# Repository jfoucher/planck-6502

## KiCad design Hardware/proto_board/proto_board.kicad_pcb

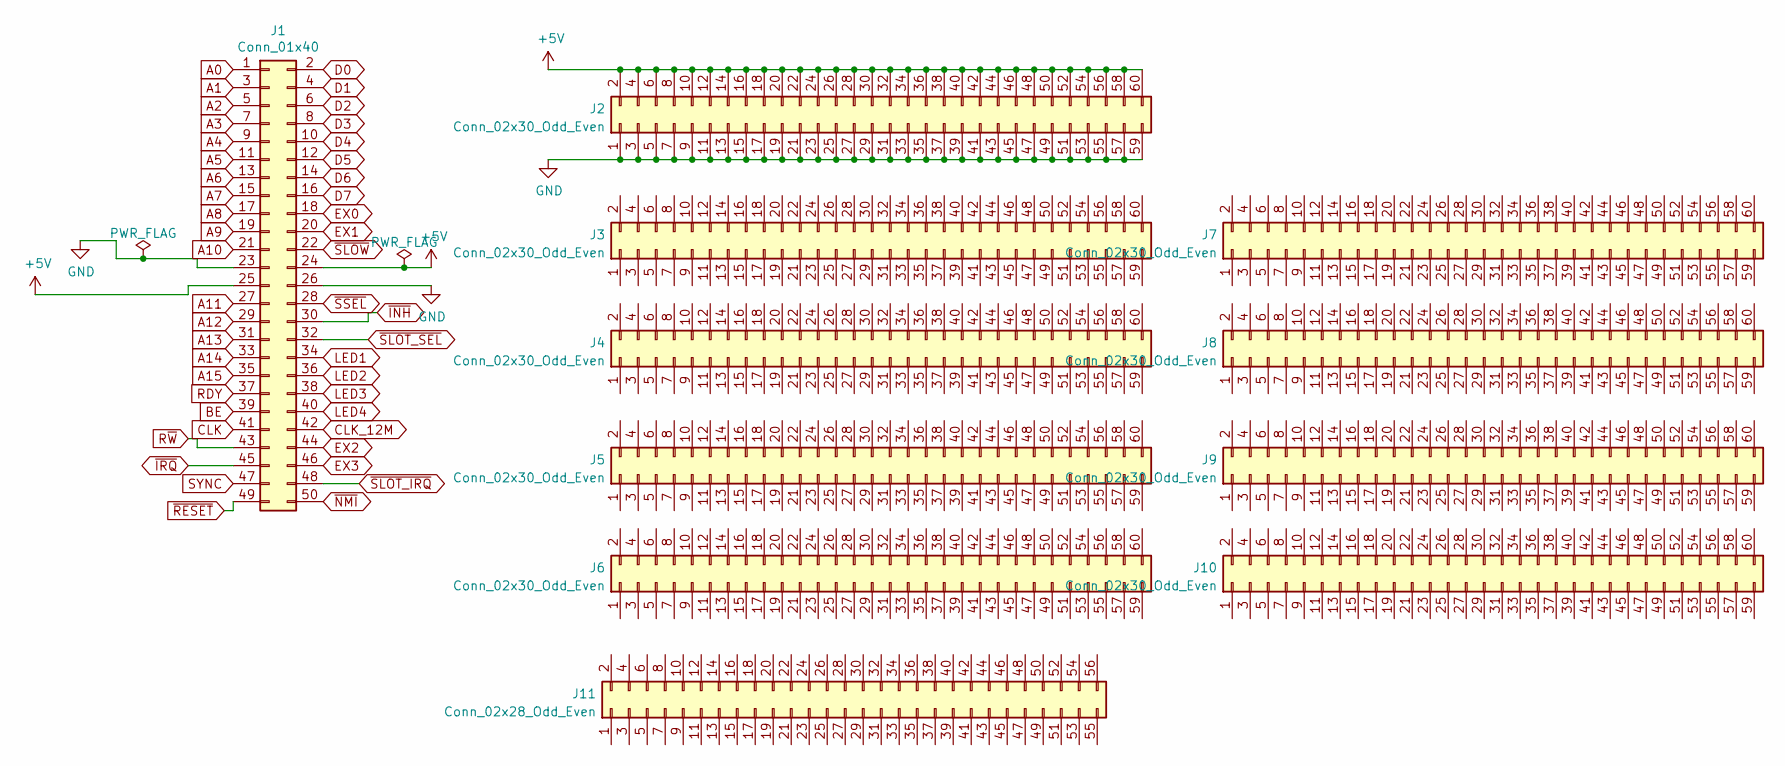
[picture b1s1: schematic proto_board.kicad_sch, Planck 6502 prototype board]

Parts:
J1: Conn_01x40; PinHeader_2x25_P2.54mm_Horizontal
J2, J3, J4, J5, J6, J7, J8, J9, J10: Conn_02x30_Odd_Even; PinHeader_2x30_P2.54mm_Vertical
J11: Conn_02x28_Odd_Even; PinHeader_2x28_P2.54mm_Vertical

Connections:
+5V: J1.24, J1.25, J2.2, J2.4, J2.6, J2.8, J2.10, J2.12, J2.14, J2.16, J2.18, J2.20, J2.22, J2.24, J2.26, J2.28, J2.30, J2.32, J2.34, J2.36, J2.38, J2.40, J2.42, J2.44, J2.46, J2.48, J2.50, J2.52, J2.54, J2.56, J2.58, J2.60
A0: J1.1
A1: J1.3
A2: J1.5
A3: J1.7
A4: J1.9
A5: J1.11
A6: J1.13
A7: J1.15
A8: J1.17
A9: J1.19
A10: J1.21
A11: J1.27
A12: J1.29
A13: J1.31
A14: J1.33
A15: J1.35
BE: J1.39
CLK: J1.41
CLK_12M: J1.42
D0: J1.2
D1: J1.4
D2: J1.6
D3: J1.8
D4: J1.10
D5: J1.12
D6: J1.14
D7: J1.16
EX0: J1.18
EX1: J1.20
EX2: J1.44
EX3: J1.46
GND: J1.23, J1.26, J2.1, J2.3, J2.5, J2.7, J2.9, J2.11, J2.13, J2.15, J2.17, J2.19, J2.21, J2.23, J2.25, J2.27, J2.29, J2.31, J2.33, J2.35, J2.37, J2.39, J2.41, J2.43, J2.45, J2.47, J2.49, J2.51, J2.53, J2.55, J2.57, J2.59
LED1: J1.34
LED2: J1.36
LED3: J1.38
LED4: J1.40
RDY: J1.37
R~W: J1.43
SYNC: J1.47
~INH: J1.30
~IRQ: J1.45
~NMI: J1.50
~RESET: J1.49
~SLOT_IRQ: J1.48
~SLOT_SEL: J1.32
~SLOW: J1.22
~SSEL: J1.28

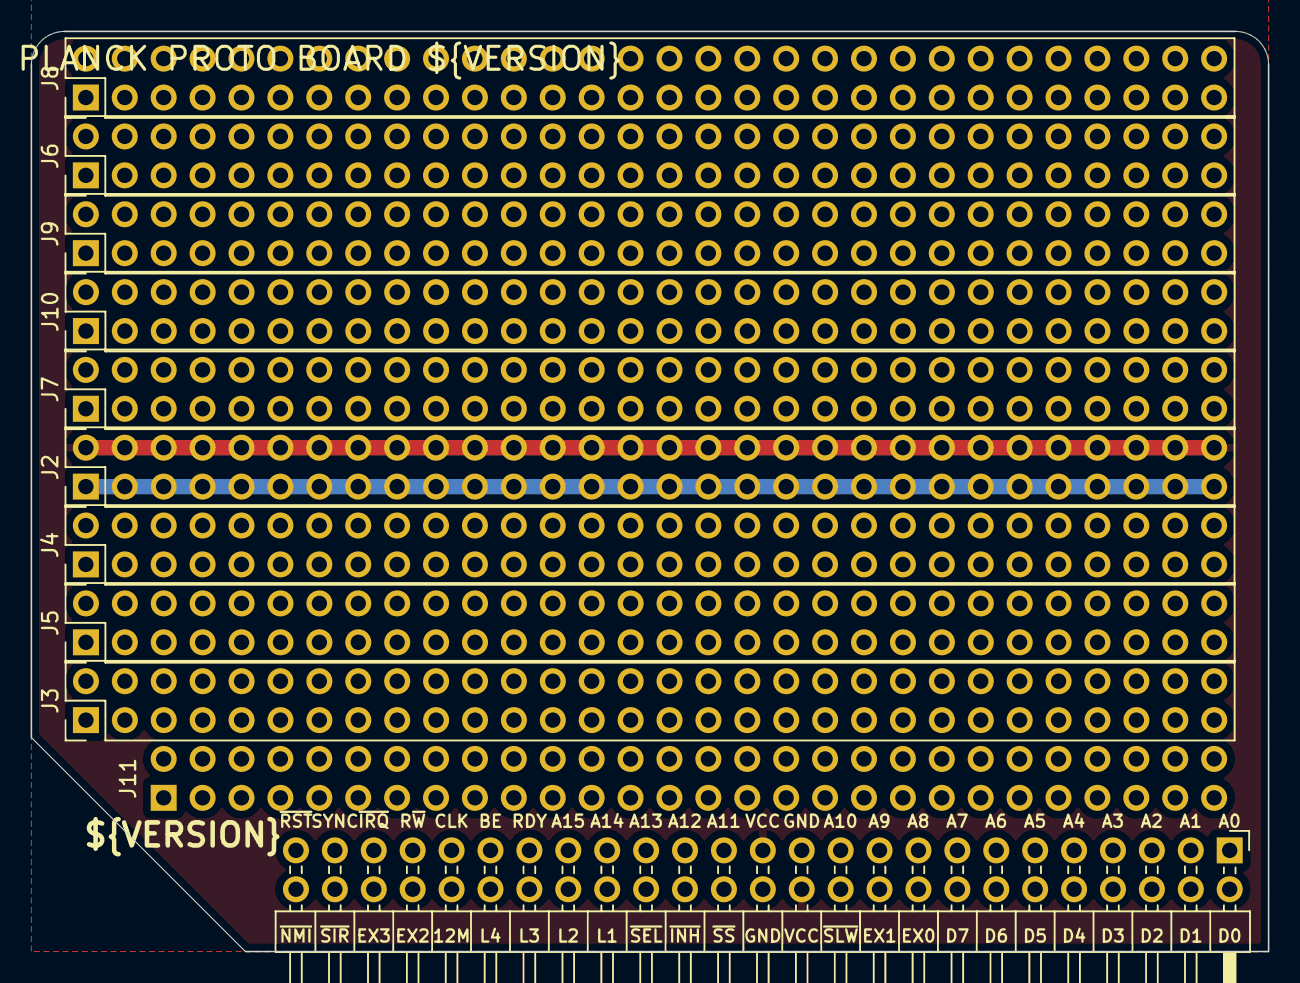
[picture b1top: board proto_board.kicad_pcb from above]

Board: 2 copper layers, 80.8 x 60.1 mm, 11 parts (0 on the bottom side), 2 nets.

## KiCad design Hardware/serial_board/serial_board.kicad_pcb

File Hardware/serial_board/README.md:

## Planck 6502 Serial board

This board uses a DWC 6551 chip to provide a serial port for the computer. It accepts a TTL serial to usb adapter.

This is what the board looks like at the moment

<br />This documentation is licensed under a <a rel="license" href="http://creativecommons.org/licenses/by-sa/4.0/">Creative Commons Attribution-ShareAlike 4.0 International License</a>.

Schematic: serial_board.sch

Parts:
C1, C2: C_Small; C_Disc_D4.3mm_W1.9mm_P5.00mm
D1, D2: LED; LED_D3.0mm
J1: Conn_01x40; PinHeader_2x25_P2.54mm_Horizontal
J2: Conn_01x06; PinSocket_1x06_P2.54mm_Vertical
R1, R2: 330R; R_Axial_DIN0204_L3.6mm_D1.6mm_P5.08mm_Horizontal
R3, R4: 10k; R_Axial_DIN0204_L3.6mm_D1.6mm_P5.08mm_Horizontal
U1: W65C51NxP; DIP-28_W15.24mm_Socket
X1: CXO_DIP8; Oscillator_DIP-8

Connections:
+5V: C1.1, C2.1, J1.24, J1.25, J2.4, R3.2, U1.15 (VCC), X1.8 (Vcc)
/RX: D2.2, J2.3, U1.12 (RxD)
/TX: D1.2, J2.2, U1.10 (TxD)
/~DSR~: J2.1, R4.2, U1.17 (~DSR)
/~DTR~: U1.11 (~DTR)
/~RTS~: J2.5, U1.8 (~RTS)
A0: J1.1, U1.13 (RS0)
A1: J1.3, U1.14 (RS1)
A2: J1.5
A3: J1.7
A4: J1.9
A5: J1.11
A6: J1.13
A7: J1.15
A8: J1.17
A9: J1.19
A10: J1.21
A11: J1.27
A12: J1.29
A13: J1.31
A14: J1.33
A15: J1.35
BE: J1.39
CLK: J1.41, U1.27 (ϕ2)
CLK_12M: J1.42
D0: J1.2, U1.18 (D0)
D1: J1.4, U1.19 (D1)
D2: J1.6, U1.20 (D2)
D3: J1.8, U1.21 (D3)
D4: J1.10, U1.22 (D4)
D5: J1.12, U1.23 (D5)
D6: J1.14, U1.24 (D6)
D7: J1.16, U1.25 (D7)
EX0: J1.18
EX1: J1.20
EX2: J1.44
EX3: J1.46
GND: C1.2, C2.2, J1.23, J1.26, J2.6, R1.1, R2.1, R4.1, U1.1 (VSS), U1.9 (~CTS), U1.16 (~DCD), X1.4 (GND)
LED1: J1.34
LED2: J1.36
LED3: J1.38
LED4: J1.40
unnamed: D1.1, R1.2
unnamed: D2.1, R2.2
unnamed: R3.1, U1.2 (CS1)
unnamed: U1.6 (XTAL1), X1.5 (OUT)
RDY: J1.37
R~W~: J1.43, U1.28 (R/~W)
SYNC: J1.47
~INH~: J1.30
~IRQ~: J1.45
~NMI~: J1.50
~RESET~: J1.49, U1.4 (~RES)
~SLOT_IRQ~: J1.48, U1.26 (~IRQ)
~SLOT_SEL~: J1.32, U1.3 (~CS2)
~SLOW~: J1.22
~SSEL~: J1.28

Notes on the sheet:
Added pullup here

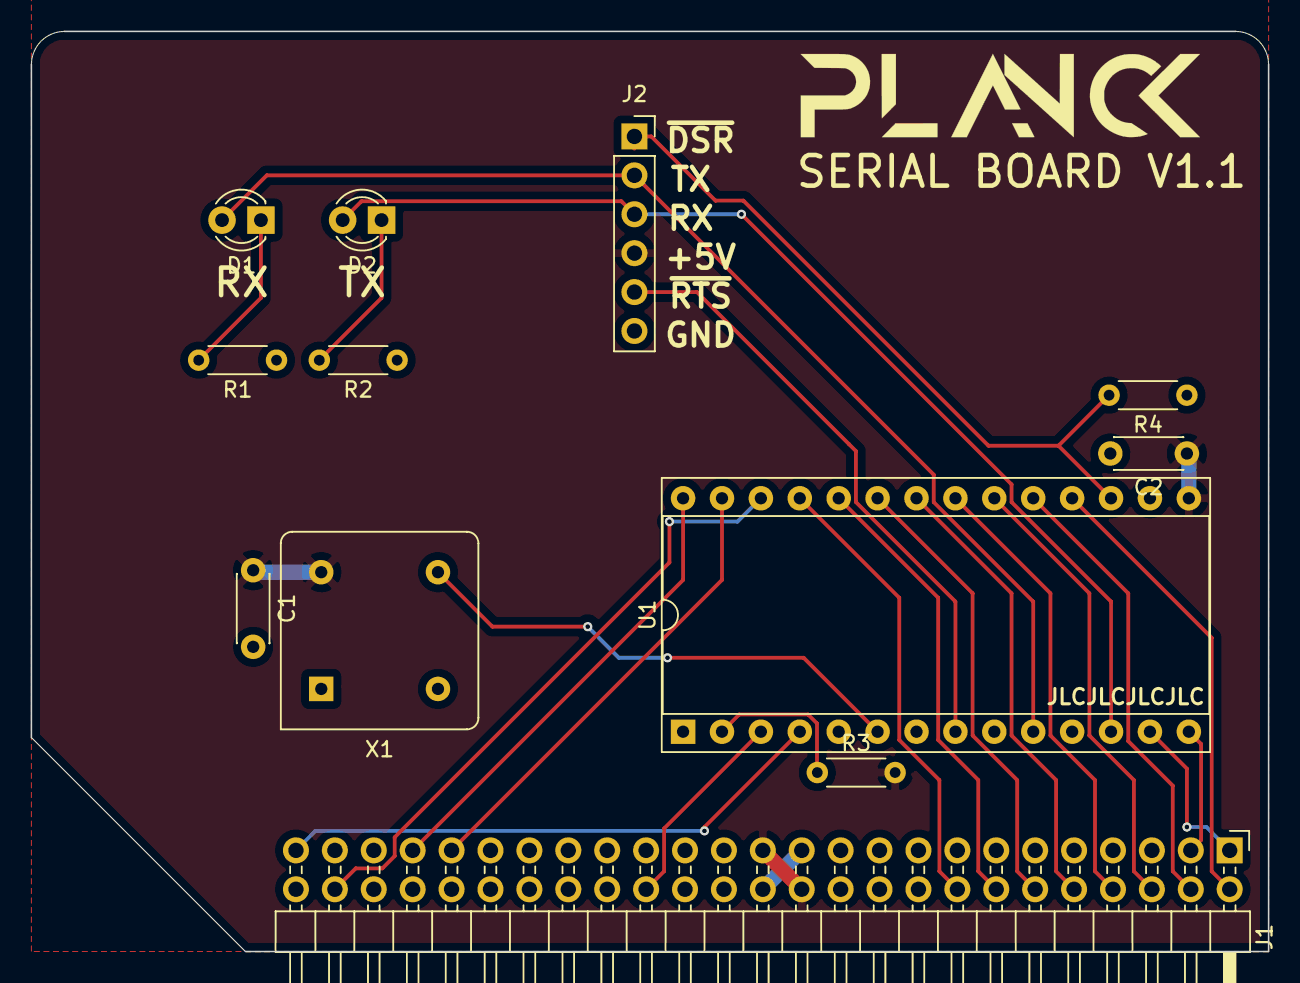
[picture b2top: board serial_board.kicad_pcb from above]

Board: 2 copper layers, 80.8 x 60.1 mm, 12 parts (0 on the bottom side), 25 nets.
